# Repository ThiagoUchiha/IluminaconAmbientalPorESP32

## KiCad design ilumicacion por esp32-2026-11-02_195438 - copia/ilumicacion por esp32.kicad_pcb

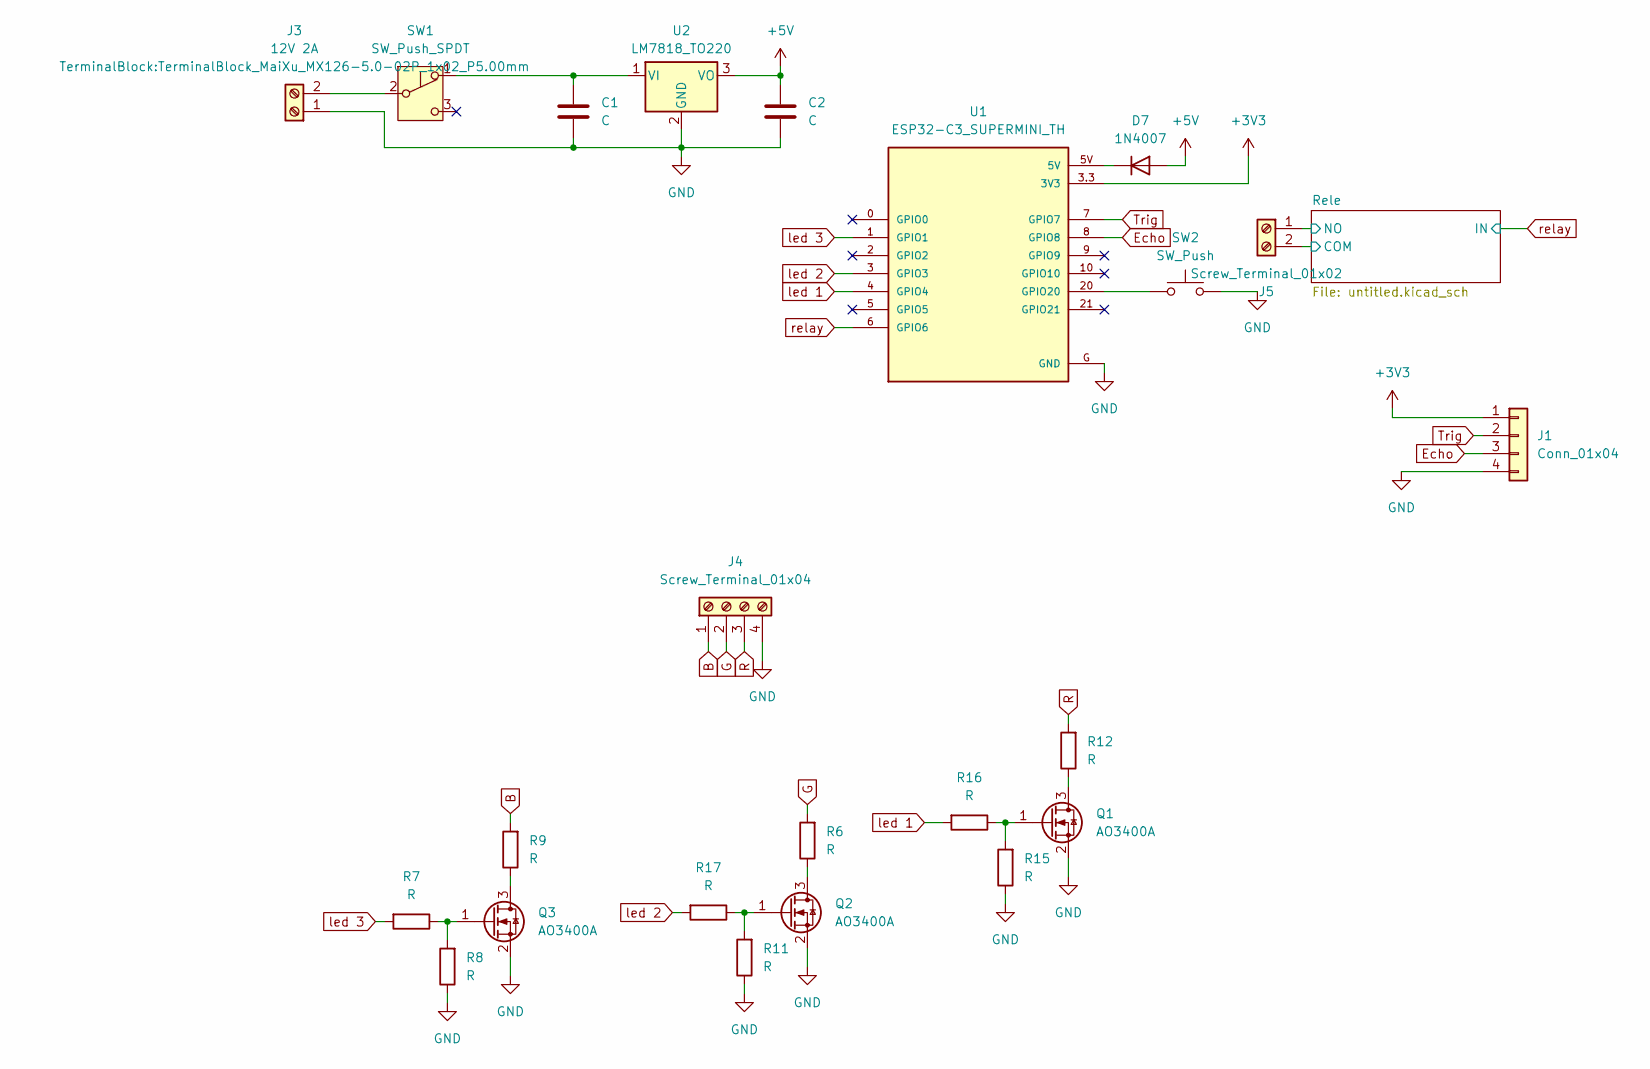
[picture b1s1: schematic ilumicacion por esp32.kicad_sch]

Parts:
C1, C2: C; C_1206_3216Metric
D7: 1N4007; D_DO-41_SOD81_P10.16mm_Horizontal
J1: Conn_01x04; PinHeader_1x04_P2.54mm_Vertical
J3: 12V 2A; TerminalBlock_MaiXu_MX126-5.0-02P_1x02_P5.00mm
J4: Screw_Terminal_01x04; TerminalBlock_MaiXu_MX126-5.0-04P_1x04_P5.00mm
J5: Screw_Terminal_01x02; TerminalBlock_MaiXu_MX126-5.0-02P_1x02_P5.00mm
Q1, Q2, Q3: AO3400A; SOT-23
R6, R7, R8, R9, R11, R12, R15, R16, R17: R; R_0805_2012Metric
SW1: SW_Push_SPDT; PinHeader_1x03_P2.54mm_Vertical
SW2: SW_Push; SW_PUSH_6mm_H4.3mm
U1: ESP32-C3_SUPERMINI_TH; MODULE_ESP32-C3_SUPERMINI
U2: LM7818_TO220; TO-220-3_Vertical

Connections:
+3V3: J1.1, U1.3.3 (3V3)
+5V: C2.1, D7.2 (A), U2.3 (VO); also elsewhere on the board
/Rele/COM: J5.2; also elsewhere on the board
/Rele/NO: J5.1; also elsewhere on the board
B: J4.1, R9.2
Echo: J1.3, U1.8 (GPIO8)
G: J4.2, R6.2
GND: C1.2, C2.2, J1.4, J3.1, J4.4, Q1.2 (S), Q2.2 (S), Q3.2 (S), R8.1, R11.1, R15.1, SW2.2, U1.G (GND), U2.2 (GND); also elsewhere on the board
unnamed: D7.1 (K), U1.5V
unnamed: J3.2, SW1.2 (B)
unnamed: Q1.3 (D), R12.1
unnamed: Q1.1 (G), R15.2, R16.1
unnamed: Q2.3 (D), R6.1
unnamed: Q2.1 (G), R11.2, R17.1
unnamed: Q3.3 (D), R9.1
unnamed: Q3.1 (G), R7.1, R8.2
unnamed: C1.1, SW1.1 (A), U2.1 (VI)
unnamed: SW2.1, U1.20 (GPIO20)
R: J4.3, R12.2
Trig: J1.2, U1.7 (GPIO7)
led 1: R16.2, U1.4 (GPIO4)
led 2: R17.2, U1.3 (GPIO3)
led 3: R7.2, U1.1 (GPIO1)
relay: U1.6 (GPIO6); also elsewhere on the board

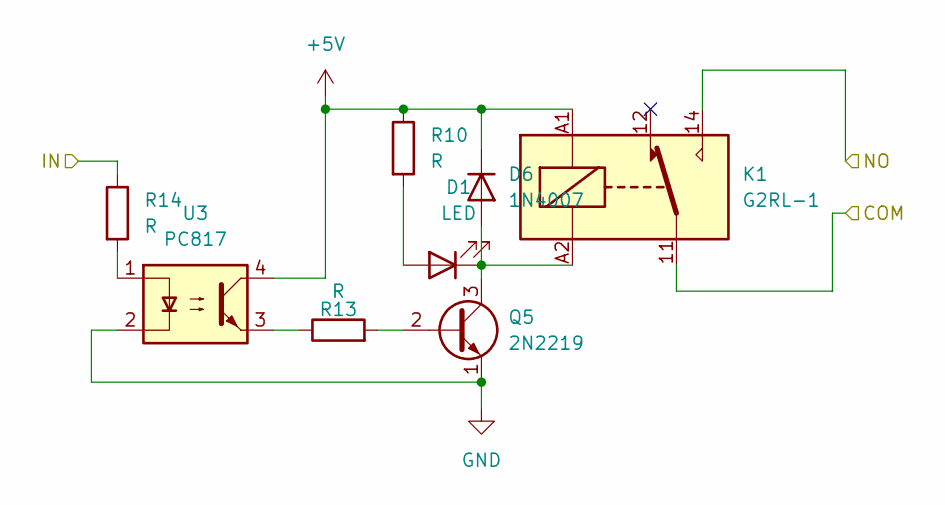
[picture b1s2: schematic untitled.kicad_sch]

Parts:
D1: LED; LED_D3.0mm_FlatTop
D6: 1N4007; D_DO-41_SOD81_P10.16mm_Horizontal
K1: G2RL-1; RELAY_SRD-05VDC-SL-C
Q5: 2N2219; TO-92L
R10, R13, R14: R; R_0805_2012Metric_Pad1.20x1.40mm_HandSolder
U3: PC817; DIP-4_W7.62mm

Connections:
+5V: D6.1 (K), K1.A1, R10.1, U3.4; also elsewhere on the board
/Rele/COM: K1.11; also elsewhere on the board
/Rele/NO: K1.14; also elsewhere on the board
GND: Q5.1 (E), U3.2; also elsewhere on the board
unnamed: D1.2 (A), R10.2
unnamed: D1.1 (K), D6.2 (A), K1.A2, Q5.3 (C)
unnamed: Q5.2 (B), R13.2
unnamed: R13.1, U3.3
unnamed: R14.2, U3.1
relay: R14.1; also elsewhere on the board

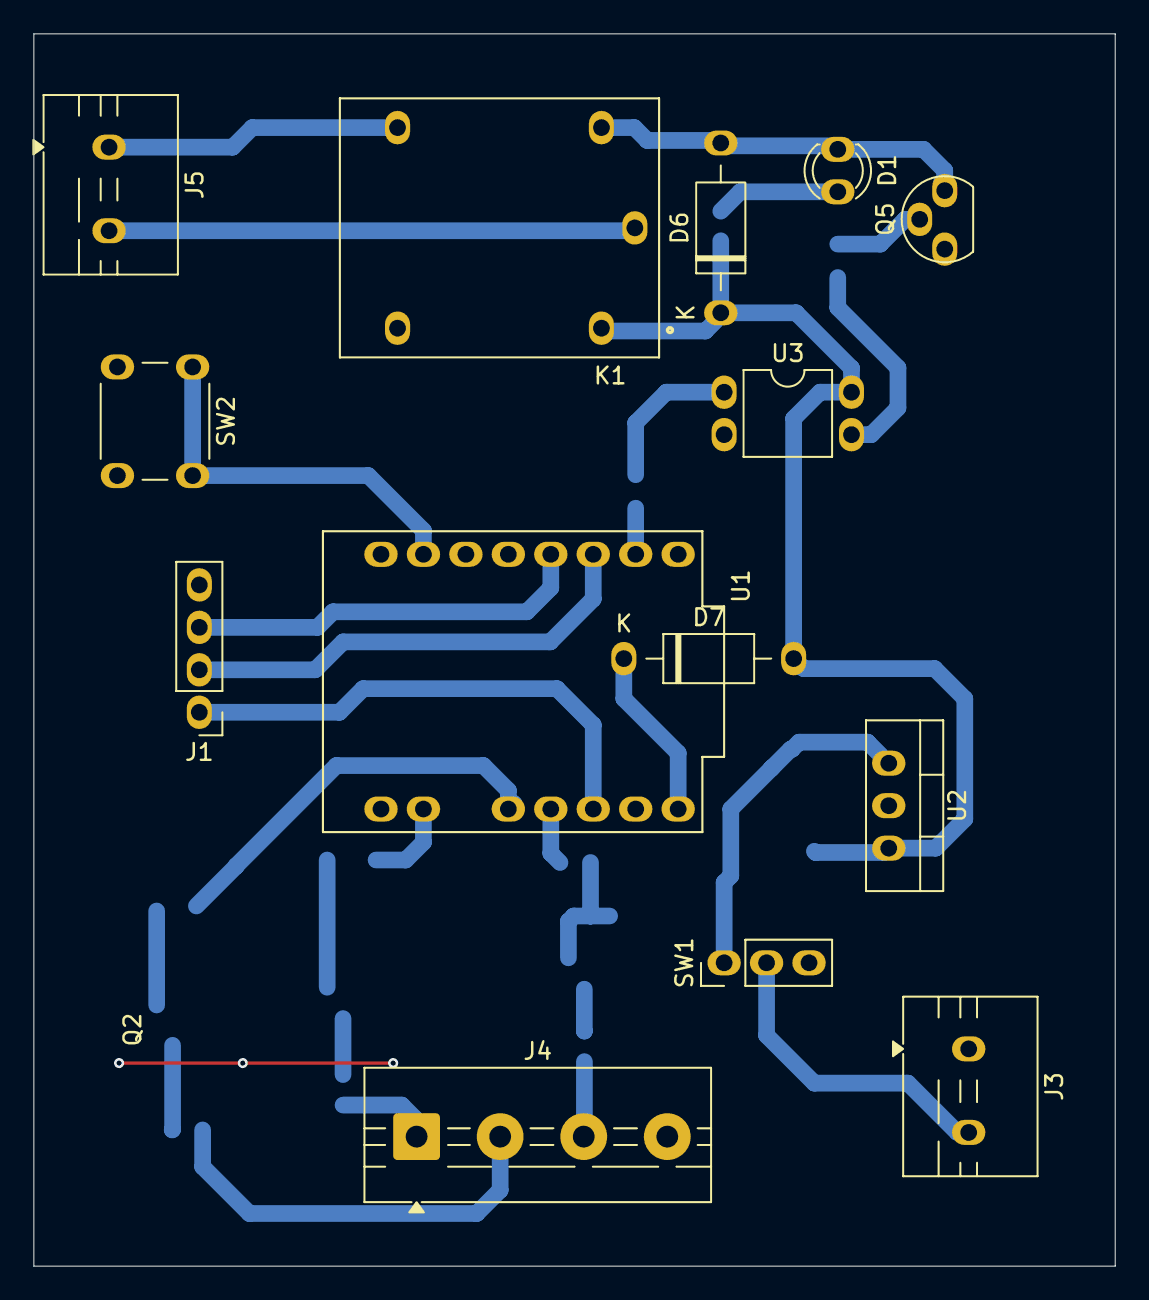
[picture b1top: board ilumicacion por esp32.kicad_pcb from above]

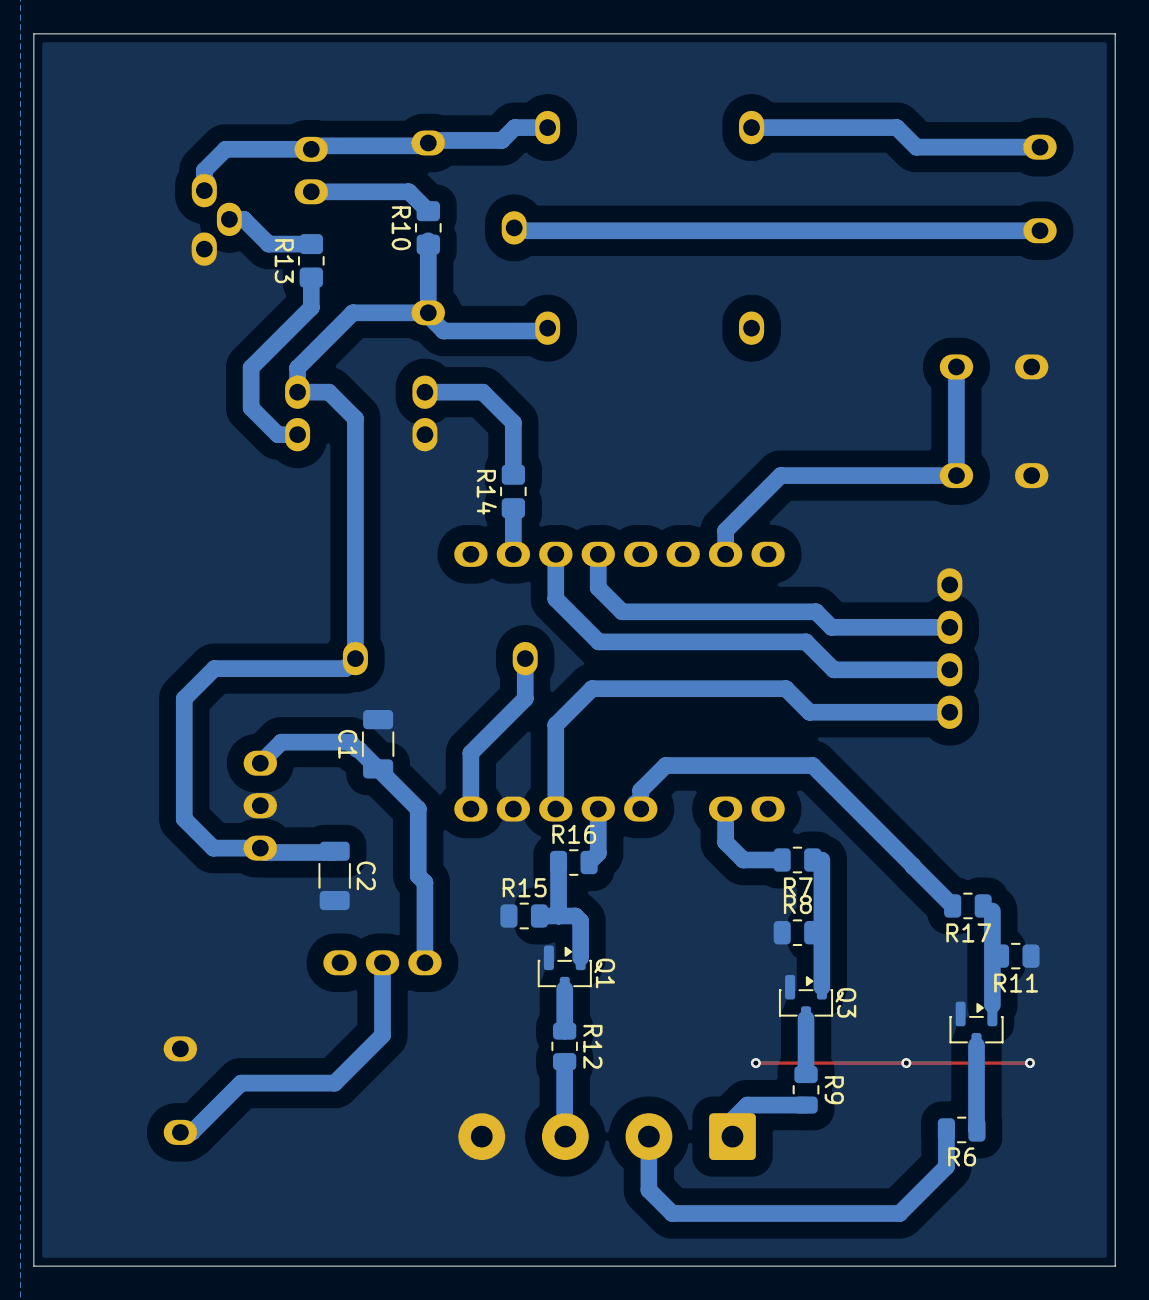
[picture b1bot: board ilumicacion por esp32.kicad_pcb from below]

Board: 2 copper layers, 64.7 x 73.7 mm, 31 parts (17 on the bottom side), 29 nets.
